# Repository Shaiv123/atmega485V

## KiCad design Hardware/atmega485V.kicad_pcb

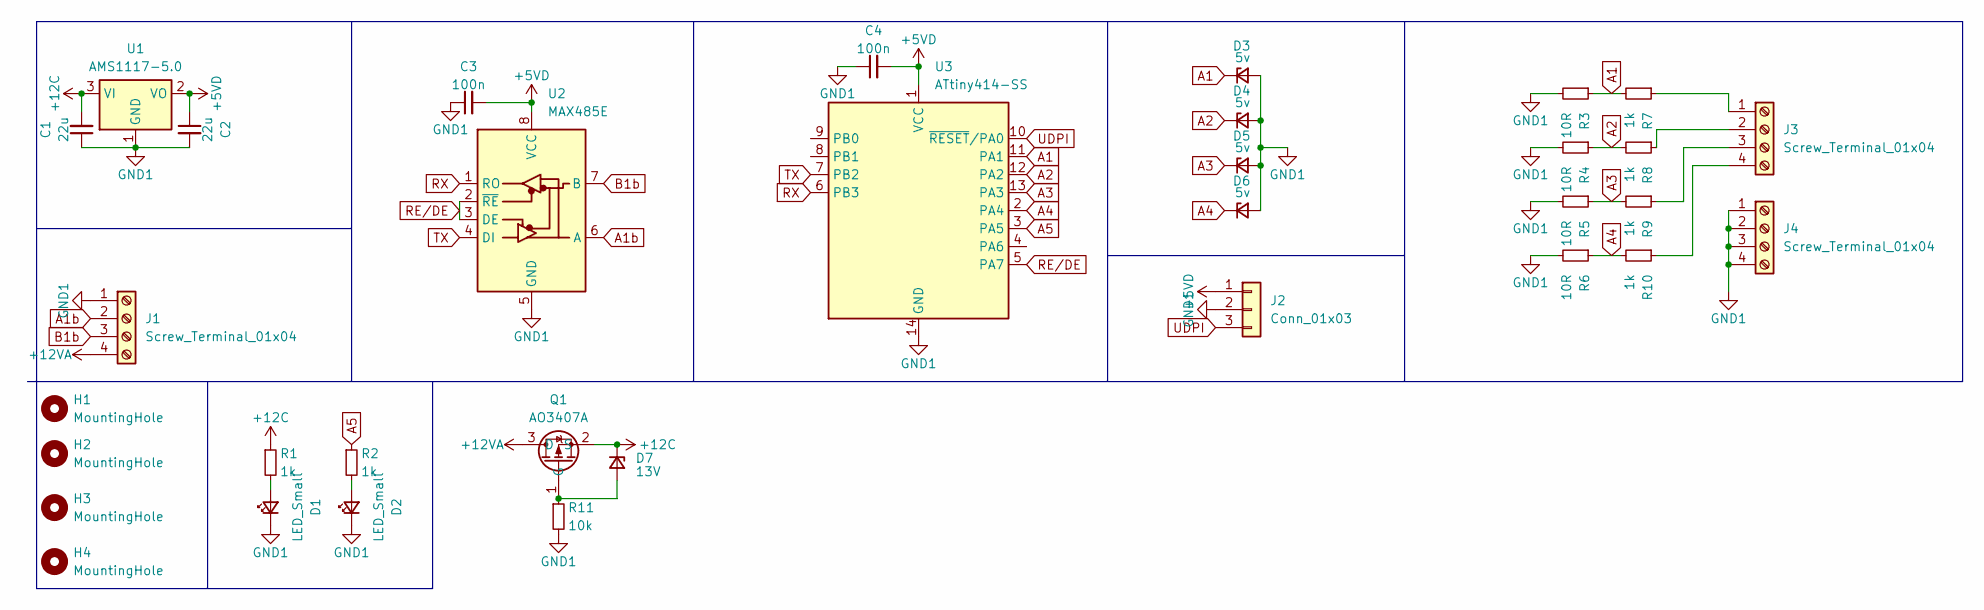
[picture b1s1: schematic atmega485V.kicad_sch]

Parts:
C1, C2: 22u; C_0805_2012Metric_Pad1.18x1.45mm_HandSolder
C3, C4: 100n; C_0805_2012Metric_Pad1.18x1.45mm_HandSolder
D1, D2: LED_Small; LED_0805_2012Metric_Pad1.15x1.40mm_HandSolder
D3, D4, D5, D6: 5v; D_MiniMELF_Handsoldering
D7: 13V; D_SOD-323_HandSoldering
H1, H2, H3, H4: MountingHole; MountingHole_3.2mm_M3_Pad_TopBottom
J1: Screw_Terminal_01x04; PhoenixContact_MC_1,5_4-G-3.81_1x04_P3.81mm_Horizontal
J2: Conn_01x03; PinHeader_1x03_P2.54mm_Vertical
J3, J4: Screw_Terminal_01x04; TerminalBlock_RND_205-00069_1x04_P7.50mm_Horizontal
Q1: AO3407A; SOT-23-3
R1, R2: 1k; R_0805_2012Metric_Pad1.20x1.40mm_HandSolder
R3, R4, R5, R6: 10R; R_2512_6332Metric_Pad1.40x3.35mm_HandSolder
R7, R8, R9, R10: 1k; R_2512_6332Metric_Pad1.40x3.35mm_HandSolder
R11: 10k; R_0805_2012Metric_Pad1.20x1.40mm_HandSolder
U1: AMS1117-5.0; SOT-223-3_TabPin2
U2: MAX485E; SO-8_3.9x4.9mm_P1.27mm
U3: ATtiny414-SS; SOIC-14_3.9x8.7mm_P1.27mm

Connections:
+5VD: C2.1, C3.2, C4.2, J2.1, U1.2 (VO), U2.8 (VCC), U3.1 (VCC)
+12C: C1.2, D7.1 (K), Q1.2 (S), R1.1, U1.3 (VI)
+12VA: J1.4, Q1.3 (D)
A1: D3.1 (K), R3.1, R7.2, U3.11 (PA1)
A1b: J1.2, U2.6 (A)
A2: D4.1 (K), R4.1, R8.2, U3.12 (PA2)
A3: D5.1 (K), R5.1, R9.2, U3.13 (PA3)
A4: D6.1 (K), R6.1, R10.2, U3.2 (PA4)
A5: R2.1, U3.3 (PA5)
B1b: J1.3, U2.7 (B)
GND1: C1.1, C2.2, C3.1, C4.1, D1.1 (K), D2.1 (K), D3.2 (A), D4.2 (A), D5.2 (A), D6.2 (A), J1.1, J2.2, J4.1, J4.2, J4.3, J4.4, R3.2, R4.2, R5.2, R6.2, R11.2, U1.1 (GND), U2.5 (GND), U3.14 (GND)
unnamed: D1.2 (A), R1.2
unnamed: D2.2 (A), R2.2
unnamed: D7.2 (A), Q1.1 (G), R11.1
unnamed: J3.1, R7.1
unnamed: J3.2, R8.1
unnamed: J3.3, R9.1
unnamed: J3.4, R10.1
RE/DE: U2.2 (~RE), U2.3 (DE), U3.5 (PA7)
RX: U2.1 (RO), U3.6 (PB3)
TX: U2.4 (DI), U3.7 (PB2)
UDPI: J2.3, U3.10 (~RESET/PA0)

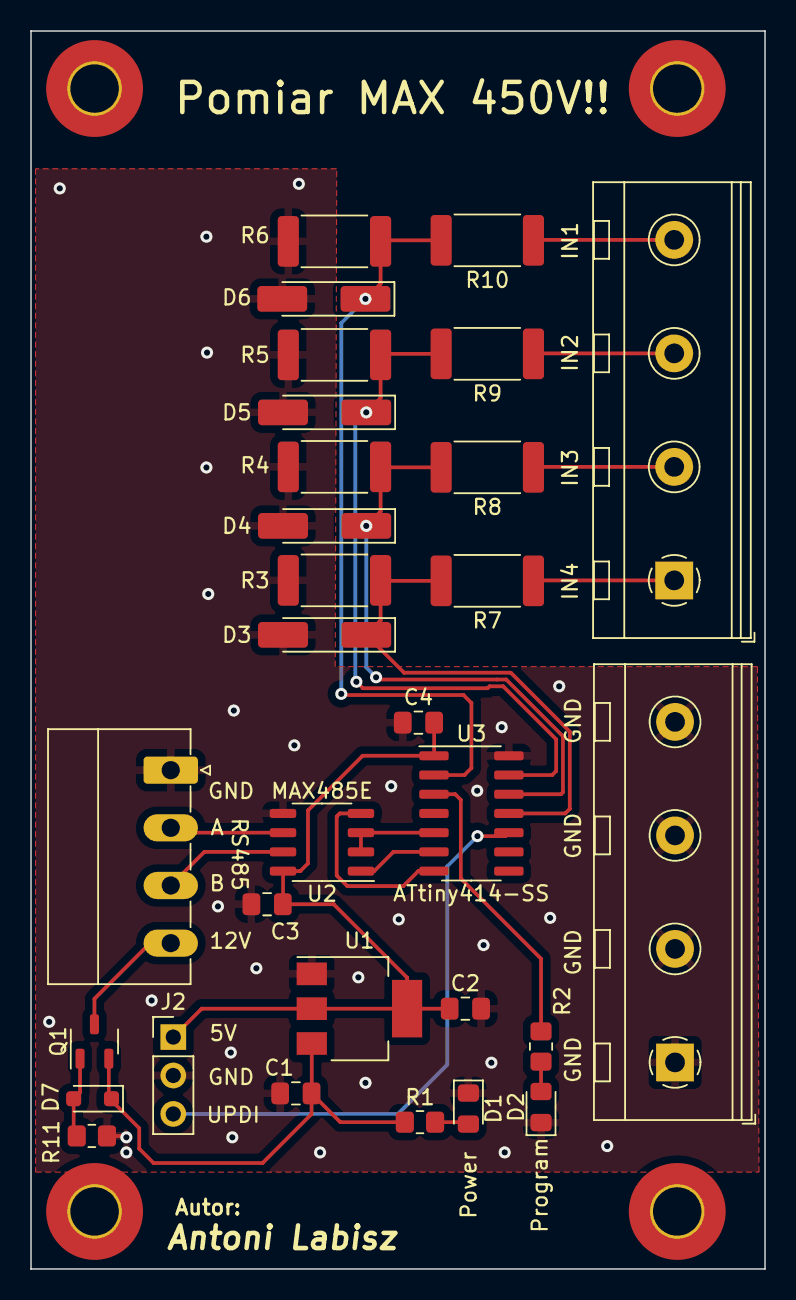
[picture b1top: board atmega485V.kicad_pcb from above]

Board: 2 copper layers, 48.5 x 81.8 mm, 34 parts (0 on the bottom side), 22 nets.
